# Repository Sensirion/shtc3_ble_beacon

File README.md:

# SHTC3 BLE Beacon
Small CR2032 battery driven BLE beacon with Sensirion's humidity and temperature sensor

## Clone this repository
```
git clone --recursive https://github.com/Sensirion/shtc3_ble_beacon.git
```

## Repository content
* firmware (hex files and source code to program the microcontroller)
* schematics (schematics, PCB layout and gerber files)
* housing (STEP file for the housing parts)
* software (software to read out the beacon data with a Raspberry Pi)

## Firmware
The firmware is based on the example of nordics ble_app_beacon in their nRF SDK. So only the modified files are in this repository. 

* To create your own verison of the firmware install the nRF5 SDK v17 from nordic https://www.nordicsemi.com/Software-and-tools/Software/nRF5-SDK/Download#infotabs
* You might want to install the nRF command line tools as well to flash the firmware and the softdevice https://infocenter.nordicsemi.com/index.jsp?topic=%2Fug_nrf52840_dk%2FUG%2Fcommon%2Fnordic_tools.html
* In addition you have to install the arm cross compiler in version gcc-arm-none-eabi-7-2018-q2-update https://developer.arm.com/tools-and-software/open-source-software/developer-tools/gnu-toolchain/gnu-rm/downloads

Afterwards unzip the SDK. Go to the directory nRF5_SDK_17.0.2/examples/ble_peripheral/ble_app_beacon and replace the file "main.c" and add "shtc3.h" and "shtc3.c". Afterwards broswse the subfolder nRF5_SDK_17.0.2/examples/ble_peripheral/ble_app_beacon/pca10040/s132/config and replace the "sdk_config.h". 
As this example was tested with the armgcc replace the Makefile in the subfolder nRF5_SDK_17.0.2/examples/ble_peripheral/ble_app_beacon/pca10040/s132/armgcc.
If you prefer another compiler you have to include the following files to the example.
 * $(SDK_ROOT)/components/ble/ble_advertising/ble_advertising.c \
 * $(SDK_ROOT)/integration/nrfx/legacy/nrf_drv_twi.c \
 * $(SDK_ROOT)/modules/nrfx/drivers/src/nrfx_twi.c \
 * $(SDK_ROOT)/modules/nrfx/drivers/src/nrfx_twim.c \
 * $(PROJ_DIR)/shtc3.c \

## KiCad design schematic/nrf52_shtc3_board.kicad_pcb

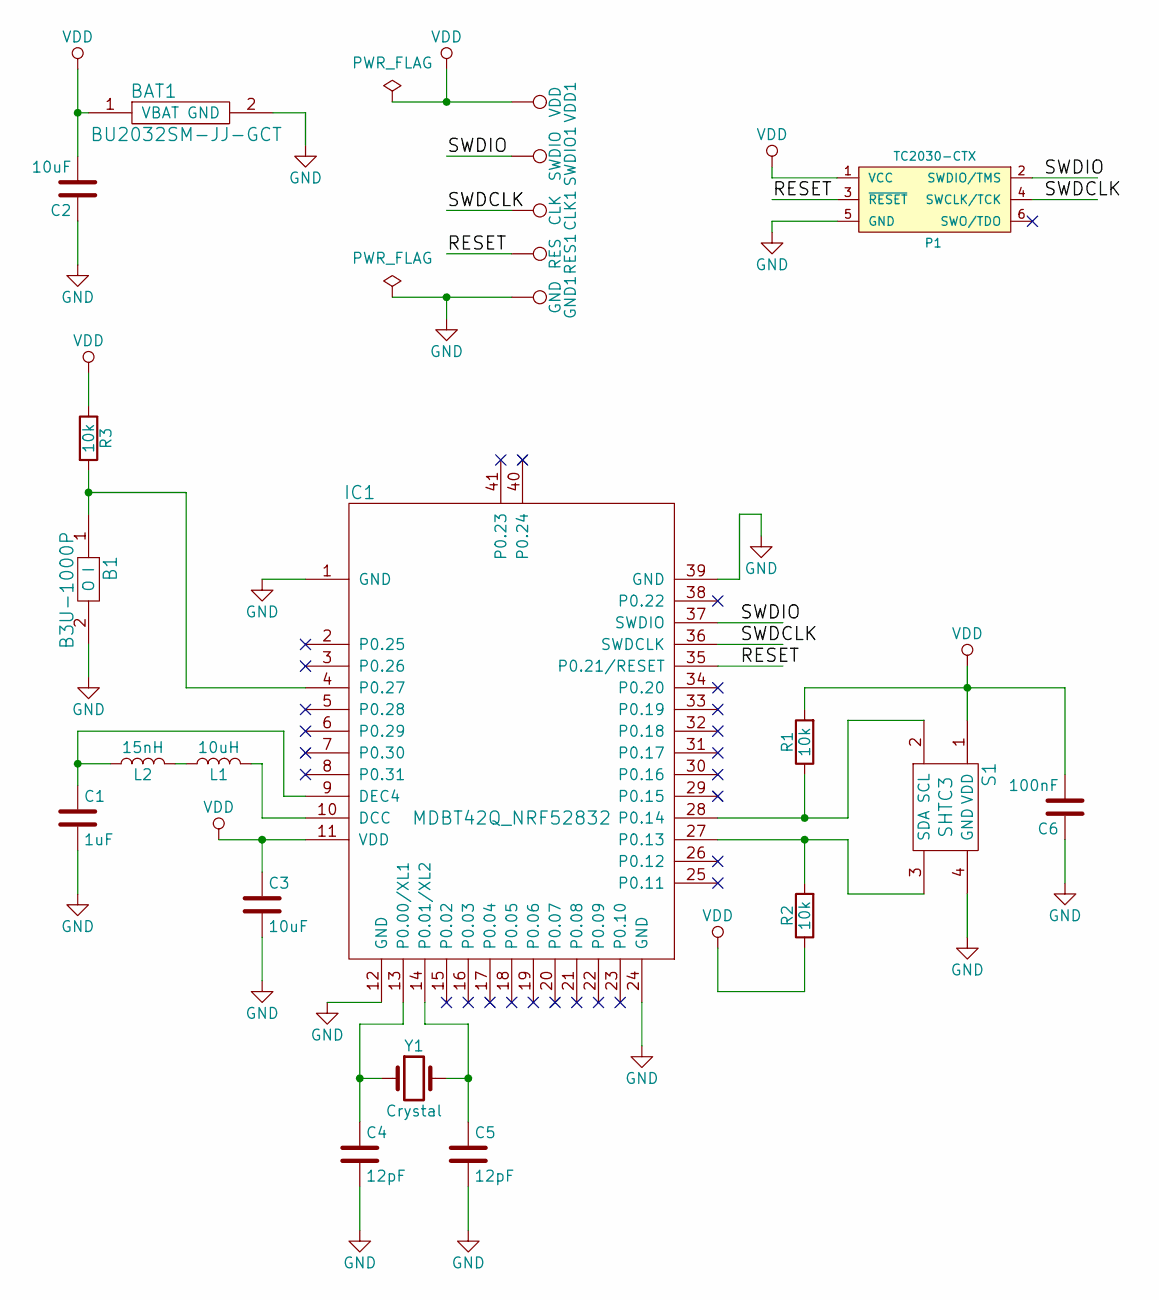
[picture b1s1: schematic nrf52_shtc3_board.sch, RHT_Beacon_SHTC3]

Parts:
B1: B3U-1000P; SW_SPST_B3U-1000P
BAT1: BU2032SM-JJ-GCT; BAT_Holder_2032
C1: 1uF; C_0603
C2, C3: 10uF; C_0603
C4, C5: 12pF; C_0603
C6: 100nF; C_0603
CLK1: CLK; WirePad_1mm_SMD
GND1: GND; WirePad_1mm_SMD
IC1: MDBT42Q_NRF52832; RF_Module_42_pin
L1: 10uH; C_0603
L2: 15nH; C_0603
P1: TC2030-CTX; TC2030-NL_SMALL
R1, R2, R3: 10k; R_0603
RES1: RES; WirePad_1mm_SMD
S1: SHTC3; DFN_4_pin_2x2
SWDIO1: SWDIO; WirePad_1mm_SMD
VDD1: VDD; WirePad_1mm_SMD
Y1: Crystal; Crystal_1.6x1_2pad

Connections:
/RESET: IC1.35 (P0.21/RESET), P1.3 (~RESET~), RES1.1
/SWDCLK: CLK1.1, IC1.36 (SWDCLK), P1.4 (SWCLK/TCK)
/SWDIO: IC1.37 (SWDIO), P1.2 (SWDIO/TMS), SWDIO1.1
GND: B1.2 (O), BAT1.2 (GND), C1.2, C2.1, C3.2, C4.2, C5.2, C6.1, GND1.1, IC1.1 (GND), IC1.12 (GND), IC1.24 (GND), IC1.39 (GND), P1.5 (GND), S1.4 (GND)
unnamed: B1.1 (I), IC1.4 (P0.27), R3.2
unnamed: C1.1, IC1.9 (DEC4), L2.1
unnamed: C4.1, IC1.13 (P0.00/XL1), Y1.1
unnamed: C5.1, IC1.14 (P0.01/XL2), Y1.2
unnamed: IC1.10 (DCC), L1.2
unnamed: IC1.27 (P0.13), R2.2, S1.3 (SDA)
unnamed: IC1.28 (P0.14), R1.1, S1.2 (SCL)
unnamed: L1.1, L2.2
VDD: BAT1.1 (VBAT), C2.2, C3.1, C6.2, IC1.11 (VDD), P1.1 (VCC), R1.2, R2.1, R3.1, S1.1 (VDD), VDD1.1

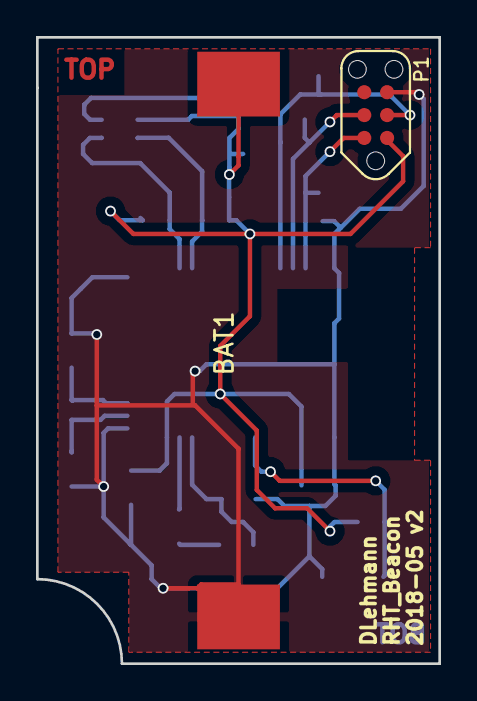
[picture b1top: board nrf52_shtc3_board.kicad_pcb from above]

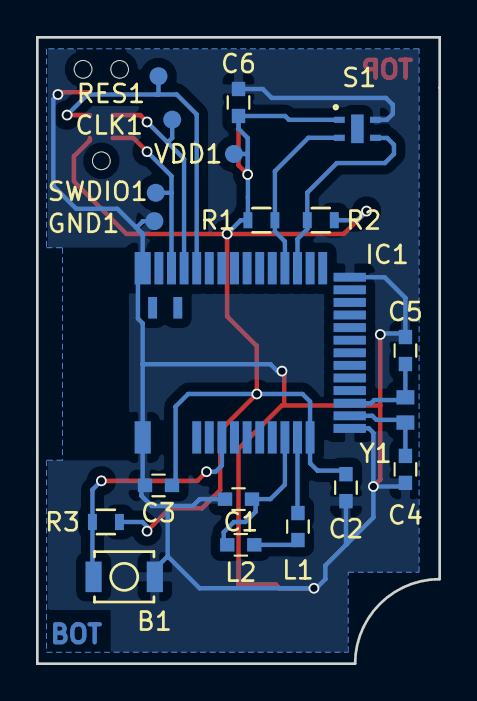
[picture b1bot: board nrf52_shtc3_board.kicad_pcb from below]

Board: 2 copper layers, 22.4 x 34.8 mm, 22 parts (20 on the bottom side), 13 nets.

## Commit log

2018-06-25 Create LICENSE
2018-06-25 Create AUTHORS
2018-06-25 Update README.md
    Add description for folder contents
2018-06-25 Add files via upload
    Add details for pcb part list
2018-06-25 Fix typo and reformat readme file
2020-01-09 Add scanner_ble_advertising as submodule
2020-01-09 Remove submodule for ble scanner
2020-01-11 Add files for webserver to show measurement data locally on a display
2020-11-30 Add firmware files
2020-11-30 Update firmware to SDK17
